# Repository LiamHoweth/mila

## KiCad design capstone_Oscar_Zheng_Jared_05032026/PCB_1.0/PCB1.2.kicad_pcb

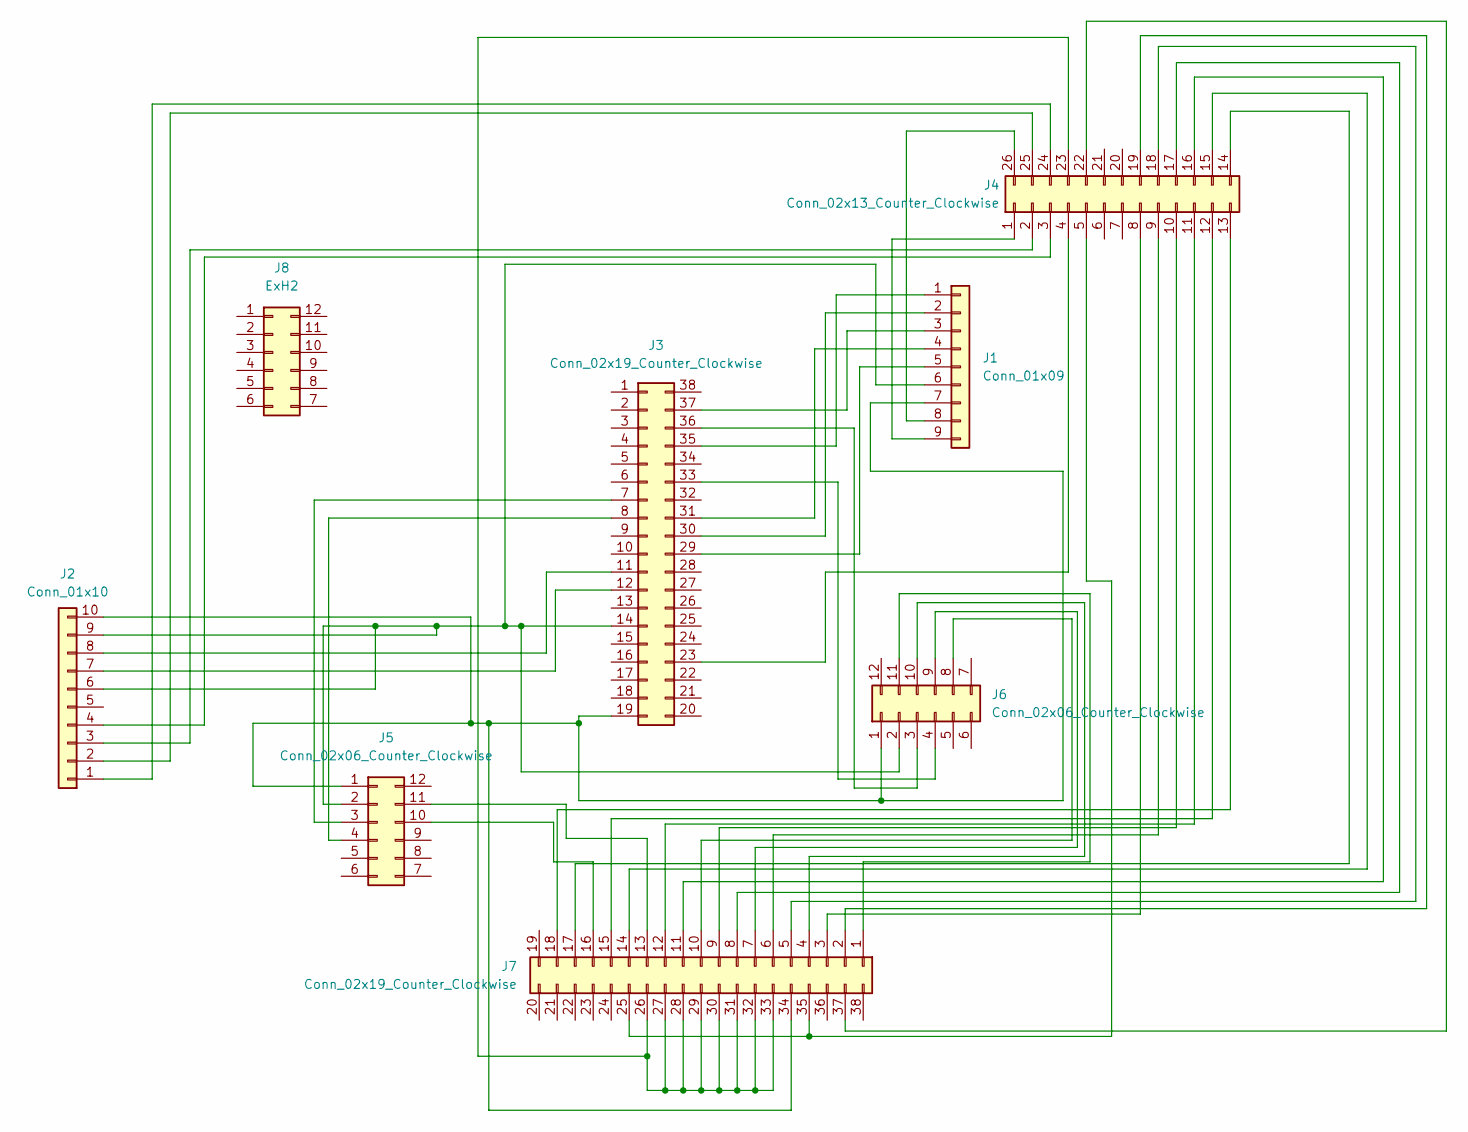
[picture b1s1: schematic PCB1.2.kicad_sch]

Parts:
J1: Conn_01x09; MCP2515
J2: Conn_01x10; ADS1115
J3: Conn_02x19_Counter_Clockwise; ESP-32
J4: Conn_02x13_Counter_Clockwise; MX23A26NF1
J5, J6: Conn_02x06_Counter_Clockwise; MCP4728
J7: Conn_02x19_Counter_Clockwise; 8-Relay Module
J8: ExH2; ExH12

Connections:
unnamed: J1.1, J3.35
unnamed: J1.2, J3.30
unnamed: J1.3, J3.37
unnamed: J1.4, J3.31
unnamed: J1.5, J3.29
unnamed: J1.6, J2.6, J2.9, J3.14, J5.2, J6.2
unnamed: J1.7, J2.10, J3.19, J5.1, J6.1, J7.34
unnamed: J1.8, J4.26
unnamed: J1.9, J4.1
unnamed: J2.1, J4.24
unnamed: J2.2, J4.25
unnamed: J2.3, J4.2
unnamed: J2.4, J4.3
unnamed: J2.7, J3.12
unnamed: J2.8, J3.11
unnamed: J3.7, J5.3
unnamed: J3.8, J5.4
unnamed: J3.23, J4.4
unnamed: J3.33, J6.4
unnamed: J3.36, J6.3
unnamed: J4.5, J7.25, J7.35
unnamed: J4.8, J7.3
unnamed: J4.9, J7.6
unnamed: J4.10, J7.9
unnamed: J4.11, J7.12
unnamed: J4.12, J7.15
unnamed: J4.13, J7.18
unnamed: J4.14, J7.17
unnamed: J4.15, J7.14
unnamed: J4.16, J7.11
unnamed: J4.17, J7.8
unnamed: J4.18, J7.5
unnamed: J4.19, J7.2
unnamed: J4.22, J7.37
unnamed: J4.23, J7.26, J7.27, J7.28, J7.29, J7.30, J7.31, J7.32, J7.33
unnamed: J5.10, J7.16
unnamed: J5.11, J7.13
unnamed: J6.8, J7.10
unnamed: J6.9, J7.7
unnamed: J6.10, J7.4
unnamed: J6.11, J7.1

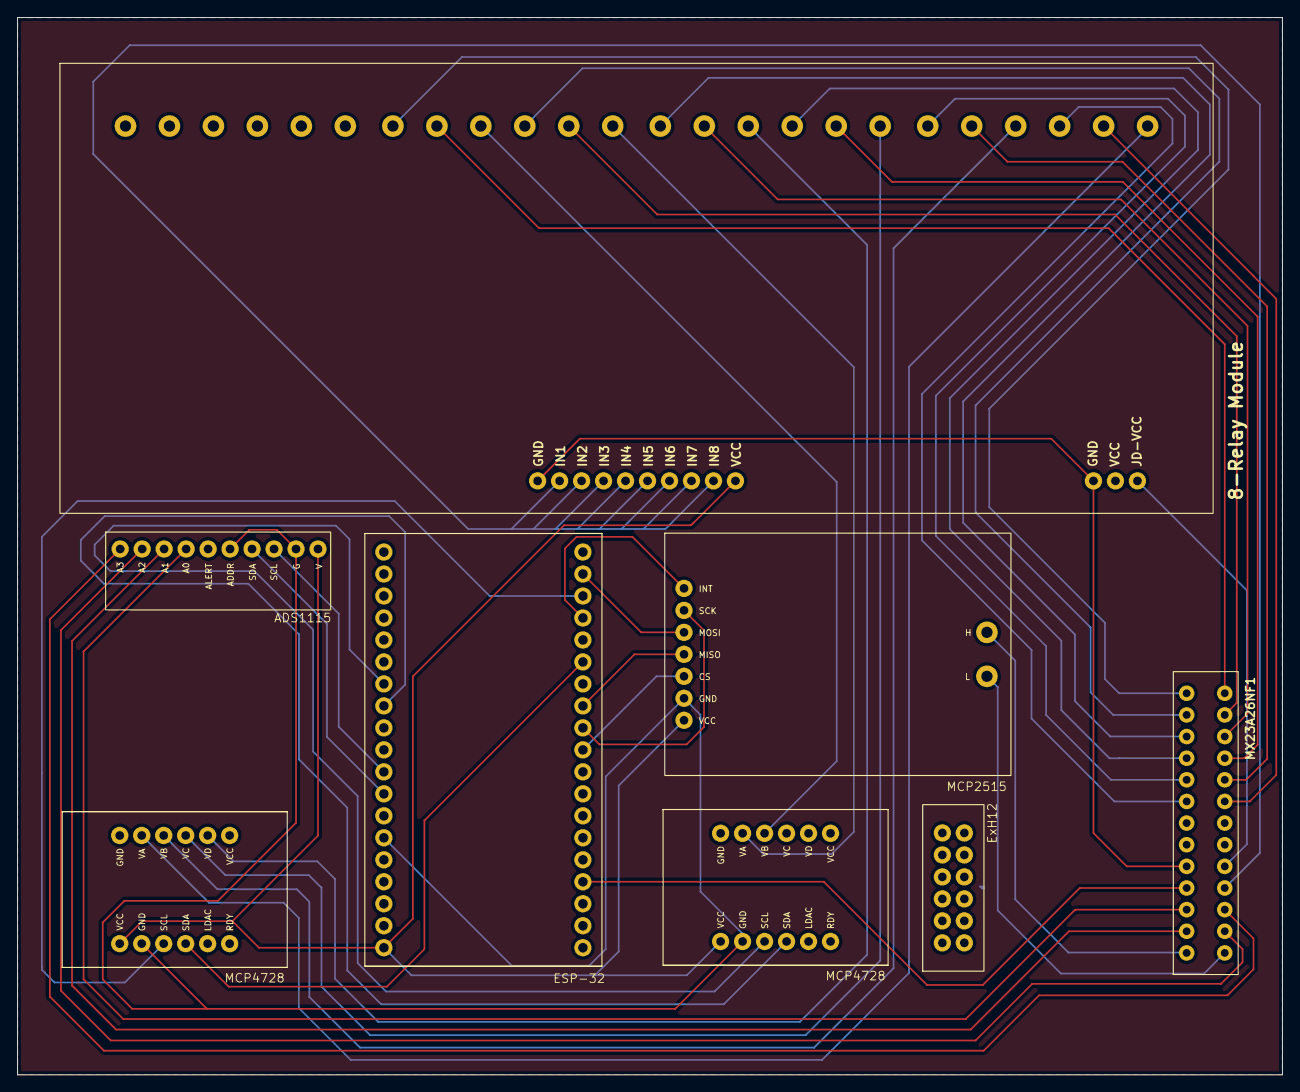
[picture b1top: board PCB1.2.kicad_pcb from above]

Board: 2 copper layers, 146.2 x 122.2 mm, 8 parts (0 on the bottom side), 41 nets.

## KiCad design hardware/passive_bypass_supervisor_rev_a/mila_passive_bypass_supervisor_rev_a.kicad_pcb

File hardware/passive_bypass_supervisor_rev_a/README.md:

# MiLa external relay supervisor — bench Rev A

This auxiliary circuit inhibits relay-coil power until rail health, a windowed firmware heartbeat, READY, held physical enable, and a fresh physical ARM press are present. It clears permission on a recognized fault and requires another ARM press after recovery. It is an isolated, room-temperature simulator prototype. Neither this circuit nor a passing CAD check establishes vehicle safety, uninterrupted signals, contact position, or independent command plausibility.

The schematic contains complete manufacturer-numbered pin connections and passive values. Custom pin-block symbols preserve real pin electrical types; identical named nets are connected. `pin_net.csv` and `netlist.xml` expose the actual circuit for audit. The carrier contains the coil drivers and four nonlatching DPDT relays. This supervisor has no signal contacts or ESP socket. The routed 80 × 60 mm, two-layer PCB has 64 circuit parts plus four mounting holes. Native ERC, DRC, unconnected-item and schematic-parity checks are all zero. Physical assembly and validation remain pending.

## Files and reproduction

- `mila_passive_bypass_supervisor_rev_a.kicad_sch`: editable complete circuit.
- `schematic.pdf` and `svg/`: exported schematic.
- `MiLaBench.kicad_sym`, `sym-lib-table`, `.kicad_pro`: local symbol library/project.
- `bom.csv`, `pin_net.csv`, `circuit.json`: parts, pin connections and board-generator input.
- `netlist.xml`: KiCad-exported connectivity, rather than a copy of the generator manifest.
- `erc.rpt`: KiCad electrical-rules report. No ERC exclusions are used.
- `bench_expectations.csv`: 33 physical probes, all PENDING.
- `.kicad_pcb`, project-local `.pretty` libraries and `fp-lib-table`: editable routed layout and local footprint copies.
- `pcb_validation/`: native checks, recorded export commands, final routing metrics and top/bottom/assembly previews.
- `manufacture/`: Gerbers, separate plated/unplated drill files, drill maps/report and positions CSV.

From the canonical MiLa directory:

```sh
python3 tools/build_passive_bypass_supervisor.py
/Applications/KiCad/KiCad.app/Contents/MacOS/kicad-cli sch erc --severity-all --exit-code-violations --output hardware/passive_bypass_supervisor_rev_a/erc.rpt hardware/passive_bypass_supervisor_rev_a/mila_passive_bypass_supervisor_rev_a.kicad_sch
/Applications/KiCad/KiCad.app/Contents/MacOS/kicad-cli sch export netlist --format kicadxml --output hardware/passive_bypass_supervisor_rev_a/netlist.xml hardware/passive_bypass_supervisor_rev_a/mila_passive_bypass_supervisor_rev_a.kicad_sch
python3 tools/build_passive_bypass_supervisor.py --verify-netlist hardware/passive_bypass_supervisor_rev_a/netlist.xml
```

The final schematic checkpoint has zero ERC violations. The explicit verifier checks 207 connected component pins and nine intentionally unconnected pins against KiCad's export. Supply flags describe externally or passively driven rails; they do not represent extra physical devices. CAD checks do not test timing, startup glitches, relay transfer, current ratings or analog outputs.

Rebuild the accepted supervisor PCB with KiCad's bundled Python:

```sh
/Applications/KiCad/KiCad.app/Contents/Frameworks/Python.framework/Versions/3.9/bin/python3.9 tools/build_passive_bypass_supervisor_board.py
```

The default rebuild uses `pcb_validation/accepted_layout.json`, containing the
accepted trace/via geometry and circuit/footprint hashes. A reconstruction from
a fresh board object passed native checks and exports. The hash guard rejects
changed circuit or footprint inputs: preserve the frozen source/export files
when reproducing this revision. A new schematic/netlist export may change
metadata hashes even when its electrical connections are equivalent; inspect
and validate a revised layout rather than bypassing that guard.

Use `--validate-existing` to check/export the saved PCB. `--reroute` invokes
exploratory routing and can require local repair; it is not the accepted build
path. The final board uses 0.25 mm tracks, 0.20 mm clearance, 0.70/0.30 mm vias
and four 3.2 mm unplated mounting holes. Actual power-pin decouplers are
approximately 1.89–2.51 mm away. The heartbeat clock uses a shared trunk with
7.3625/7.9375 mm branches; measured geometry skew is 0.575 mm. Geometry alone
does not establish propagation, setup/hold or asynchronous-edge acceptance.

## Supply and connector contract

Use a protected, current-limited 5.0 V bench supply, with 4.95–5.25 V available for guaranteed monitor recovery margin, and a shared ESP 3.3 V rail. Nominal room-temperature assembly testing uses 5.0 V and 3.3 V at 20–30°C. The monitor can inhibit arming at 4.75 V even if that voltage is allowed at the carrier. Maintain a common ground. Do not apply raw vehicle power. The upstream 5 V rail supplies the DAC system and one input of the U3 supply OR; it is separate from the switched coil feed. U13 is powered from 3.3 V.

| Connector | Pin sequence | Meaning |
|---|---|---|
| J1, 1×8 | 1 GND; 2 V3V3; 3 ESP_RESET_HEADER; 4 WDI_HEADER; 5 READY_HEADER; 6 REQ_L; 7 REQ_7; 8 REQ_8 | Controller interface. Explicit GPIO mapping belongs to the controller wiring manifest. |
| J2, 1×2 | 1 V5_SUP; 2 GND | Upstream protected regulated 5 V. |
| J3, 1×4 | 1 V5_SUP; 2 V5_COIL_SWITCHED; 3 V3V3; 4 DEADMAN_HEADER | External held two-pole normally-open enable: coil pole connects 1–2, auxiliary pole connects 3–4 only while held. |
| J4, 1×2 | 1 ARM_SW; 2 GND | Separate physical normally-open ARM button. |
| J5, 1×7 | 1 GND; 2 V5_COIL_SWITCHED; 3 COIL_PERMIT; 4 REQ_L; 5 REQ_7; 6 REQ_8; 7 CARRIER_5V_FEEDBACK | Carrier interface, including returned post-enable coil input. Match functions, not arbitrary connector pin numbers. |
| J6, 1×6 | 1 GND; 2 HEALTH_OK; 3 QUALIFIED; 4 HB_GOOD; 5 ARMED; 6 ZERO_REQ | 3.3 V status/test points. |

The generic 2.54 mm headers are bench connectors. Give the physical harness keyed connectors, strain relief and clear pin labels before any later integration. For J3 select **C&K 8221SHZGE**, a held DPDT momentary pushbutton using its two normally-open contacts only. Its gold-over-silver contacts support both 1 A at 28 V DC power switching and low-level/dry-circuit use; the auxiliary contact switches about 0.33 mA at 3.3 V. The manufacturer warns that the two poles need not make/break simultaneously. Connect J3-1 to switch COM1, J3-2 to NO2, J3-3 to COM4, and J3-4 to NO5. Insulate unused NC3 and NC6. Verify purchased terminal identity by continuity: released 1–3/4–6, pressed 1–2/4–5. A stable toggle or a firmware switch does not implement this held-enable requirement.

For J4 select **C&K 8125SHZBE**, a gold-contact SPDT momentary pushbutton: J4-1 to COM1, J4-2 to NO2, with NC3 insulated. Its 0.4 VA/20 V maximum dry-circuit rating covers the approximately 3.3 mA initial ARM-capacitor discharge and about 33 µA held current. Use insulated short 22 AWG leads, panel mounting and strain relief; label the independent buttons ENABLE and ARM. `external_bom.csv` records these off-board parts. Do not jumper J3 for acceptance testing that claims a physical power cut.

J5 must be wired by function to the carrier `GND`, `5V_RAW`, `COIL_PERMIT`, `REQ_GROUP`, `REQ_K7`, `REQ_K8`, and returned `5V_RAW` inputs respectively. `V5_COIL_SWITCHED` is the carrier's `5V_RAW`; it must not also be tied to upstream V5_SUP. J5-7 is returned through the carrier control connector JCTRL1-6 and tied directly to the carrier's post-physical-enable, pre-Q5 `5V_RAW`. Do not loop J5-7 to J5-2 locally: that would defeat control-connector continuity detection. This is a 5 V sense conductor to R22, never an ESP signal. Connect no downstream bulk storage capacitor to the coil feed. No USB, ESP 5 V pin, DAC rail or other source may backfeed it.

READY/WDI/request inputs are nominal 3.3 V and use short local wires. The assembled supervisor adds a 10 kΩ ground load to each request; the carrier adds further loads, particularly two driver loads to REQ_GROUP. Verify controller HIGH ≥2.60 V and carrier MOSFET gate ≥2.50 V under the complete loading. Contact-board input tolerance of 5.25 V does not permit applying 5 V to a connected ESP GPIO.

COIL_PERMIT is a supervisor-generated nominal 3.3 V signal intended solely for the carrier's AO3400A permission gate. Keep it separate from ESP GPIOs and status points. CARRIER_5V_FEEDBACK is a distinct 5 V wire that must never connect to the ESP.

## Exact supervision and state behavior

U1, TPS3430WQDRCRQ1, is the external window watchdog. Both VDD pins and its exposed pad are connected. R1 = 10 kΩ pulls CWD high; SET0 and SET1 are hard-wired low; R2 = 10 kΩ pulls CRST high. No GPIO can disable the watchdog. The falling-edge interval's lower bound is 7.65–10.35 ms and upper bound is 92.7–125.4 ms. Use 30 ms between falling edges, with a 1 ms HIGH pulse, after successful completion of three 10 ms application iterations. WDO remains low for 8.5–11.5 ms after a watchdog fault. It automatically attempts recovery, but the ARM latch does not automatically recover.

The watchdog startup has special timing: WDO is held low during startup/reset; the first subsequent falling WDI edge starts a window whose lower-bound check is suppressed. The separate heartbeat qualification is therefore necessary. A static HIGH/LOW cannot establish ongoing health. Do not generate WDI using a free-running timer, PWM, DMA or an interrupt that can continue after the actual test-control loop hangs.

U2, TPS3808G33QDBVRQ1, monitors the shared 3.3 V rail and the ESP hardware reset/enable line through its MR pin. Its nominal rail trip is 3.07 V; threshold tolerance and hysteresis apply. R3 = 100 kΩ to V3V3 selects nominal 300 ms release delay (180–420 ms specified). Connecting to an actual shared ESP rail is essential; a separate always-on supervisor rail would not detect loss of the controller's own 3.3 V.

U3, TPS3808G01QDBVRQ1, monitors **CARRIER_5V_FEEDBACK** through R22 = 100 kΩ 0.1% and R23 = 9.53 kΩ 0.1%. This observes actual coil input downstream of the physical switch and both complete carrier connectors. Sustained loss of either complete power/control connector causes this divider to fall; after the monitor recognizes the loss and clears the latch, reconnection cannot resume the previous armed state. Contact chatter shorter than the SENSE filter and supervisor recognition time need not latch a fault. C17 = 1 nF filters SENSE with about 8.7 µs nominal RC. Falling trip is nominal 4.655 V. IC accuracy and divider tolerances permit roughly 4.55–4.76 V trip; maximum hysteresis can make recovery require approximately 4.90 V. Use at least 4.95 V for arming, rather than treating 4.75 V as guaranteed recovery.

D1, BAS70-05-7-F, supplies U3 from an isolated OR of both rails: pin 1 anode V3V3, pin 2 anode V5_SUP, pin 3 common cathode V_PG5_SUP. U3's VDD, MR pull-high, CT/R4 and C3 use V_PG5_SUP. This keeps U3 powered when 5 V vanishes but USB keeps 3.3 V alive, and also keeps its SENSE below its supply when 5 V is present while 3.3 V is absent. A fixed G50 powered only from 5 V loses a defined output when its own supply collapses; powering it from 3.3 V while sensing 5 V would exceed recommended SENSE≤VDD. The divider plus diode OR removes those live-rail conflicts. Measure V_PG5_SUP and backfeed in every power sequence; do not infer behavior in the unspecified near-zero-supply region from absolute maximum ratings.

U1 WDO, U2 RESET and U3 RESET are open-drain and share HEALTH_N, pulled to V3V3 by R5 = 10 kΩ. No push-pull output is tied to that node. U4 is a Schmitt buffer for the open-drain edge; U5 buffers the physical-enable sense. U8/U9 form:

```text
QUALIFIED = HEALTH_OK AND READY AND DEADMAN_OK
ZERO_REQ  = NOT(REQ_L OR REQ_7 OR REQ_8)
```

QUALIFIED drives the asynchronous active-low clear pins on both U10 heartbeat stages and the U11 ARM latch. Recognized rail/reset/watchdog/READY/enable loss therefore clears both heartbeat qualification and ARM.

U6 inverts WDI so its falling edge clocks both U10 stages. The first accepted edge after qualification sets HB_ONE. R24 = 1 kΩ, C18 = 100 pF C0G 5%, and U14 SN74LVC1G17QDCKRQ1 delay and buffer HB_ONE into HB_ONE_SAFE before the second D input. A later accepted falling edge sets HB_GOOD. This observations chain requires a full inter-edge interval after READY and held enable; it does not independently prove the semantic validity of a firmware iteration.

R24/C18 provide approximately 100 ns nominal RC plus buffer delay, preserving positive same-clock hold margin. At the datasheet's 3 V threshold test point, U14 VT+ = 1.36–2.04 V, VT− = 0.77–1.35 V; U14 propagation is 1.5–8 ns at 3.3 V ±0.3 V. Use the actual threshold, R/C tolerance, source levels, loading and routing skew to verify:

```text
tCQ(min) + tRC-rise(min) + tU14(min) > tD-hold + positive clock skew
tCQ(max) + tRC-rise(max) + tU14(max) + tD-setup < next heartbeat interval
tRC-fall(max) + tU14(max) < minimum qualified-low time before a new heartbeat
```

The LVC74A requires data setup ≥3 ns, hold ≥1 ns, clear-inactive setup ≥2 ns and clear/clock pulse duration ≥3.3 ns at 3.3 V ±0.3 V. Its clock-to-Q is 1–5.2 ns. The exact 3.3 V Schmitt threshold and slow-edge delay are not separately bounded by the table's 3 V threshold row; measure the actual stage rather than asserting an interpolated certified limit. For the bench protocol, require QUALIFIED LOW ≥10 µs, hold request/READY states stable ≥1 ms before ARM, and start post-recovery heartbeat edges ≥1 ms after qualification. Hardware rail/watchdog release delays greatly exceed RC flush time. Test coincident asynchronous edges separately.

U12 sets ARM_D = HB_GOOD AND ZERO_REQ. U11 captures this only on a physical ARM rising edge. R6 = 100 kΩ, R7 = 1 kΩ and C14 = 1 µF form the ARM network; U6's Schmitt inverter makes pressing the normally-open button produce that edge. Press discharge is about 1 ms and release is about 100 ms nominal, subject to thresholds and capacitance. Verify actual contact bounce. A button held through a fault remains a constant clock level: restoring QUALIFIED does not create a fresh ARM clock edge. Release the button long enough for ARM_CLK to return LOW, then press it again. Requests must be LOW at this new edge.

U13 **SN74LVC1G08QDCKRQ1**, powered from V3V3, produces COIL_PERMIT only when ARMED AND QUALIFIED are high. R18 = 1 kΩ limits initial gate current; R19 = 82 kΩ and the carrier's RPD6 = 82 kΩ pull permission LOW while keeping static loading light. The carrier RG6 remains 330 Ω; R20/R21 remain 10 kΩ input pulldowns; C13 bypasses V3V3. This avoids relying on a 5 V AHCT driver's undefined behavior below its 4.5 V operating range during 5 V collapse.

TI's current LVC1G08-Q1 Rev H specifies recommended-temperature VOH ≥VCC−0.15 V at 100 µA, and Ioff ≤10 µA magnitude at VCC=0. With both 82 kΩ pulldowns, the complete static load is at most approximately **86.51 µA** at VCC=3.6 V, including 1% resistor corners and 100 nA MOSFET gate leakage. At VCC=3.0 V, VOH≥2.85 V produces calculated header ≥**2.78085 V** and Q6 gate ≥**2.76944 V**. Add no output indicator or other DC load that invalidates the 100 µA limit.

At VCC=0, a 10 µA source-like Ioff and 100 nA gate leakage give calculated Q6 gate ≤**0.41743 V** with intact pulldowns. This is a **leakage-voltage screening calculation, not a drain-current OFF guarantee**: the MOSFET threshold is measured at a specified drain current and does not bound drain current at this gate voltage. Opening either pulldown also reduces the margin. Measure Q6/Q5 gate voltage, drain behavior and coil current with V3V3=0/V5 present and through every partial 3.3 V ramp. Typical MOSFET capacitance can suggest approximately 26 µs discharge settling, but does not establish a bounded cutoff time. All these values are calculations awaiting physical validation.

## Firmware and physical boundaries

Boot/reset must keep READY and all relay requests LOW. Raise READY only after successful DAC initialization, acknowledgment of every required write, fresh command and communication checks, and measured simulator output acceptance. Stop WDI when the guarded control iteration fails. The existing autonomous AutoSweep source does not implement this contract and must not directly drive the new interface. READY LOW inhibits DAC absence only if firmware detects it and lowers READY. An ESP that keeps READY HIGH and valid WDI pulses while writing an incorrect DAC value remains outside this supervisor's detection capability.

Physical deadman release disconnects coil power even if the ARM latch or permission electronics fail high. The auxiliary contact also clears the latch. The returned carrier supply detects whole-connector loss but cannot detect an individual broken request/permission conductor while the feedback conductor stays connected. Such a conductor can resume its previously asserted state on reconnection; shorted feedback can conceal connector loss. Pole timing mismatch, welded enable contacts, stored energy, wiring shorts and backfeed remain physical test/fault-analysis matters. Releasing a nonlatching relay eventually restores its NC connection only with healthy contacts; the delay and bounce are finite. K7/K8 NC states are default connectivity, not a verified motor-off or stock-safe behavior.

The settled Boolean state model assumes valid voltages, valid minimum pulse widths, setup/hold/recovery timing and settled inputs. It cannot prove absence of metastability, narrow output pulses during arbitrary power ramps, asynchronous coincidences or stuck component faults. Bench acceptance must scope the real COIL_PERMIT, gate, coil current and every COM signal through those cases. The current design has one watchdog, one fault node and a single permission chain; it is not redundant or single-fault tolerant.

## Primary sources

- [TI TPS3430-Q1 watchdog, pins, startup and timing](https://www.ti.com/lit/ds/symlink/tps3430-q1.pdf)
- [TI TPS3808-Q1 supervisors, G01 divider, timing and supply limits](https://www.ti.com/lit/ds/symlink/tps3808-q1.pdf)
- [TI SN74LVC74A-Q1 flip-flops and timing](https://www.ti.com/lit/ds/symlink/sn74lvc74a-q1.pdf)
- [TI SN74LVC1G17-Q1 Schmitt buffers](https://www.ti.com/lit/ds/symlink/sn74lvc1g17-q1.pdf)
- [TI SN74LVC2G14-Q1 Schmitt inverters](https://www.ti.com/lit/ds/symlink/sn74lvc2g14-q1.pdf)
- [TI SN74LVC1G08-Q1 AND gates](https://www.ti.com/lit/ds/symlink/sn74lvc1g08-q1.pdf)
- [TI SN74LVC1G27 NOR gate](https://www.ti.com/lit/ds/symlink/sn74lvc1g27.pdf)
- [Diodes Incorporated BAS70-05 common-cathode array](https://www.diodes.com/datasheet/download/BAS70.pdf)
- [C&K 8020 momentary pushbuttons, pin numbers and contact ratings](https://www.ckswitches.com/media/1397/8020.pdf)
- [C&K exact 8221SHZGE and 8125SHZBE selection guide](https://www.ckswitches.com/media/2222/ck_short-form-catalogue.pdf)

U7 and D1 use catalog order codes; selecting several Q1 logic devices does not make the whole board automotive-qualified. Verify purchase availability, exact markings, all footprints and manufacturer revisions before assembly.

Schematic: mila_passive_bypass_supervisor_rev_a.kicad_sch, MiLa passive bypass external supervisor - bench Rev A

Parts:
C1, C2, C3, C4, C5, C6, C7, C8, C9, C10, C11, C12, C13, C19: 100nF X7R 10V; C_0603_1608Metric
C14, C15, C16: 1uF X7R 10V; C_0603_1608Metric
C17: 1nF C0G 10V; C_0603_1608Metric
C18: 100pF C0G 5% 10V; C_0603_1608Metric
D1: BAS70-05-7-F; SOT-23
J1: BENCH_1x08; PinHeader_1x08_P2.54mm_Vertical
J2, J4: BENCH_1x02; PinHeader_1x02_P2.54mm_Vertical
J3: BENCH_1x04; PinHeader_1x04_P2.54mm_Vertical
J5: BENCH_1x07; PinHeader_1x07_P2.54mm_Vertical
J6: BENCH_1x06; PinHeader_1x06_P2.54mm_Vertical
R1, R2, R5, R8, R9, R10, R11, R12, R13, R20, R21: 10k 1%; R_0603_1608Metric
R3, R4, R6: 100k 1%; R_0603_1608Metric
R7, R16, R18, R24: 1k 1%; R_0603_1608Metric
R14, R15, R17: 100 1%; R_0603_1608Metric
R19: 82k 1%; R_0603_1608Metric
R22: 100k 0.1%; R_0603_1608Metric
R23: 9.53k 0.1%; R_0603_1608Metric
U1: TPS3430WQDRCRQ1; VSON-10-1EP_3x3mm_P0.5mm_EP1.65x2.4mm
U2: TPS3808G33QDBVRQ1; SOT-23-6
U3: TPS3808G01QDBVRQ1; SOT-23-6
U4, U5, U14: SN74LVC1G17QDCKRQ1; SOT-353_SC-70-5
U6: SN74LVC2G14IDCKRQ1; SOT-363_SC-70-6
U7: SN74LVC1G27DCKR; SOT-363_SC-70-6
U8, U9, U12, U13: SN74LVC1G08QDCKRQ1; SOT-353_SC-70-5
U10, U11: SN74LVC74AQPWRG4Q1; TSSOP-14_4.4x5mm_P0.65mm

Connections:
/ARMED: J6.5 (ARMED), R20.1, U11.5 (1Q), U13.1 (A)
/ARM_CLK: U6.4 (2Y), U11.3 (1CLK)
/ARM_D: U11.2 (1D), U12.4 (Y)
/ARM_RC: C14.1, R6.2, R7.1, U6.3 (2A)
/ARM_SW: J4.1 (ARM_SW), R7.2
/CARRIER_5V_FEEDBACK: J5.7 (CARRIER_5V_FEEDBACK), R22.1
/COIL_PERMIT: J5.3 (COIL_PERMIT), R18.2, R19.1
/DEADMAN_HEADER: J3.4 (DEADMAN_HEADER), R17.1
/DEADMAN_OK: U5.4 (Y), U9.2 (B)
/DEADMAN_RAW: R8.1, R17.2, U5.2 (A)
/ESP_RESET_HEADER: J1.3 (ESP_RESET_HEADER), R16.1
/ESP_RESET_N: R16.2, U2.3 (MR_N)
/HB_CLK: U6.6 (1Y), U10.3 (1CLK), U10.11 (2CLK)
/HB_GOOD: J6.4 (HB_GOOD), U10.9 (2Q), U12.1 (A)
/HB_ONE: R24.1, U10.5 (1Q)
/HB_ONE_SAFE: U10.12 (2D), U14.4 (Y)
/HB_STAGE_RC: C18.1, R24.2, U14.2 (A)
/HEALTH_N: R5.2, U1.8 (WDO_N), U2.1 (RESET_N), U3.1 (RESET_N), U4.2 (A)
/HEALTH_OK: J6.2 (HEALTH_OK), U4.4 (Y), U8.1 (A)
/HEALTH_READY: U8.4 (Y), U9.1 (A)
/PERMIT_DRIVER: R18.1, U13.4 (Y)
/PG5_CT: R4.2, U3.4 (CT)
/PG33_CT: R3.2, U2.4 (CT)
/QUALIFIED: J6.3 (QUALIFIED), R21.1, U9.4 (Y), U10.1 (1CLR_N), U10.13 (2CLR_N), U11.1 (1CLR_N), U13.2 (B)
/READY: R9.1, R15.2, U8.2 (B)
/READY_HEADER: J1.5 (READY_HEADER), R15.1
/REQ_7: J1.7 (REQ_7), J5.5 (REQ_7), R12.1, U7.3 (B)
/REQ_8: J1.8 (REQ_8), J5.6 (REQ_8), R13.1, U7.6 (C)
/REQ_L: J1.6 (REQ_L), J5.4 (REQ_L), R11.1, U7.1 (A)
/V5_COIL_SWITCHED: J3.2 (V5_COIL_SWITCHED), J5.2 (V5_COIL_SWITCHED)
/V5_SENSE: C17.1, R22.2, R23.1, U3.5 (SENSE)
/WDI: R10.1, R14.2, U1.7 (WDI), U6.1 (1A)
/WDI_HEADER: J1.4 (WDI_HEADER), R14.1
/WD_CRST: R2.2, U1.4 (CRST)
/WD_CWD: R1.2, U1.2 (CWD)
/ZERO_REQ: J6.6 (ZERO_REQ), U7.4 (Y), U12.2 (B)

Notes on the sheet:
BENCH ONLY: regulated 5.0 V + shared ESP 3.3 V; keep disconnected from vehicle.
Hardware: window watchdog + both rail supervisors + physical held enable + READY -> asynchronous latch clear.
Two post-READY WDI falling edges -> HB_GOOD; fresh physical ARM rising edge with requests all LOW -> ARMED.
3.3 V COIL_PERMIT is only for relay gate input. External enable pole J3(1-2) physically interrupts coil power.
J5 pin 7 returns carrier post-enable/pre-cutoff 5 V: R22 monitors actual feed; never connect this 5 V wire to ESP.
A. POWER AND WATCHDOG: rail monitors remain independent of the ESP application.
B. QUALIFICATION AND ARM: asynchronous fault clear; two heartbeat stages; fresh physical ARM edge.
J3: external held DPST-NO enable, no jumper in deployed setup. J4: separate normally-open ARM button.
Output is not a semantic command/plausibility monitor. Driver/relay/ECU timing requires measured bench validation.
C. OUTPUT AND INTERFACES: 3.3 V permission is for the carrier MOSFET gate only; carrier feedback is 5 V.
D. PASSIVES: connected by named nets; place each U's 100 nF physically at its supply pins.
E. SUPPLY FLAGS: rails are externally driven or passively fed; flags are not physical components.

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
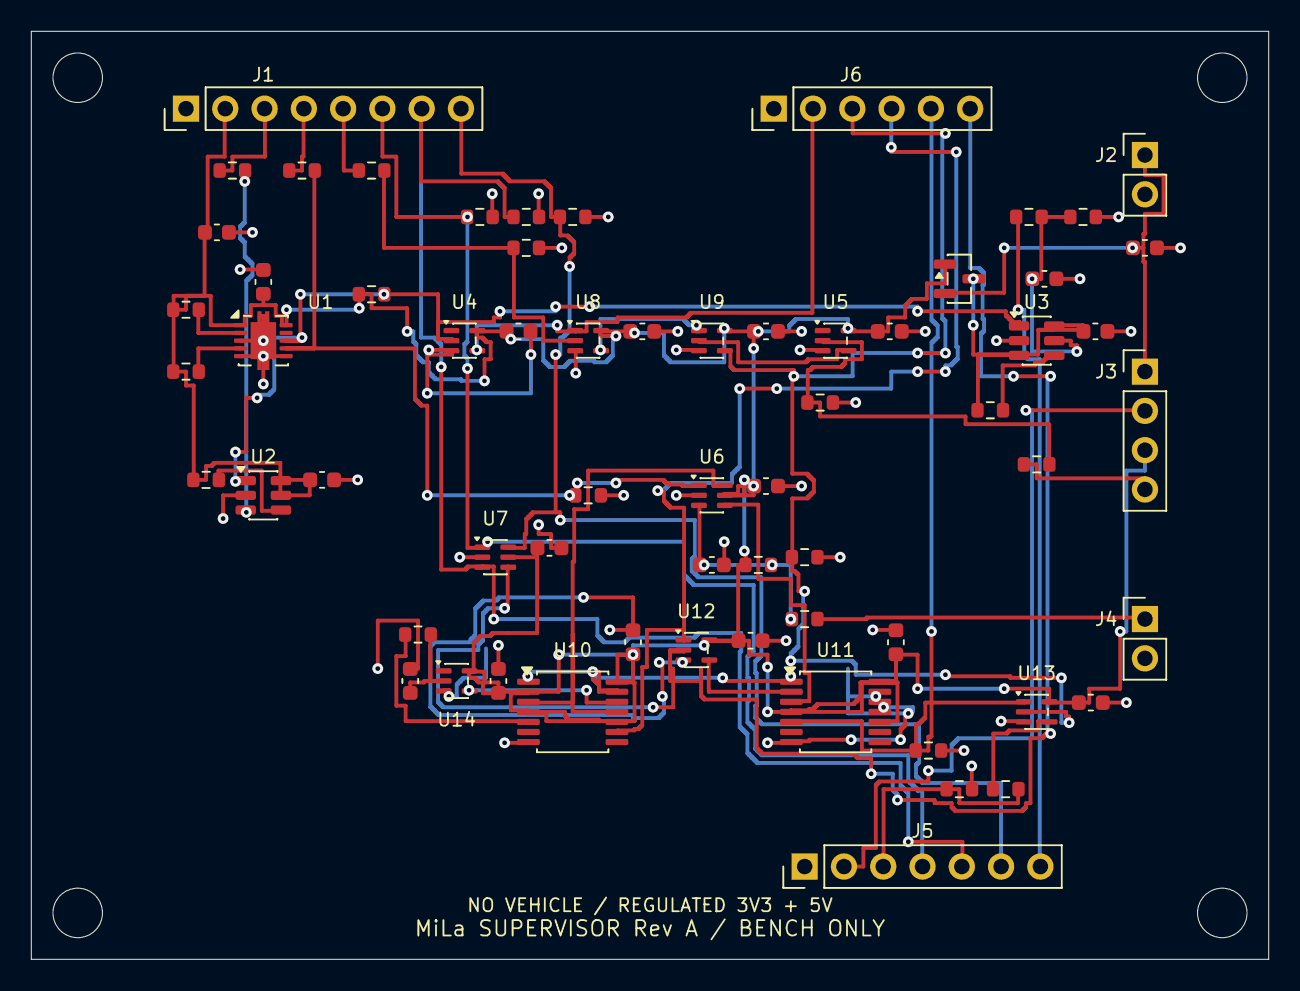
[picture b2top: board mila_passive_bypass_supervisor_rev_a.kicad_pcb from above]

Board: 2 copper layers, 80.0 x 60.0 mm, 68 parts (0 on the bottom side), 40 nets.

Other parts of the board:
H1, H2, H3, H4: MountingHole_3.2mm

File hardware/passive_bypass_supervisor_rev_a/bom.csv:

reference,value,footprint,role,manufacturer_datasheet
U1,TPS3430WQDRCRQ1,Package_SON:VSON-10-1EP_3x3mm_P0.5mm_EP1.65x2.4mm,Independent window watchdog; fixed hardware settings,https://www.ti.com/lit/ds/symlink/tps3430-q1.pdf
U2,TPS3808G33QDBVRQ1,Package_TO_SOT_SMD:SOT-23-6,3.3 V and ESP hardware reset supervisor,https://www.ti.com/lit/ds/symlink/tps3808-q1.pdf
U3,TPS3808G01QDBVRQ1,Package_TO_SOT_SMD:SOT-23-6,5 V adjustable monitor supplied by isolated diode-OR of both rails,https://www.ti.com/lit/ds/symlink/tps3808-q1.pdf
D1,BAS70-05-7-F,Package_TO_SOT_SMD:SOT-23,Low-leakage supply OR keeps 5 V monitor alive when either rail disappears,https://www.diodes.com/datasheet/download/BAS70.pdf
U4,SN74LVC1G17QDCKRQ1,Package_TO_SOT_SMD:SOT-353_SC-70-5,Clean open-drain fault edges before ordinary logic,https://www.ti.com/lit/ds/symlink/sn74lvc1g17-q1.pdf
U5,SN74LVC1G17QDCKRQ1,Package_TO_SOT_SMD:SOT-353_SC-70-5,Clean physical enable auxiliary-contact edges,https://www.ti.com/lit/ds/symlink/sn74lvc1g17-q1.pdf
U6,SN74LVC2G14IDCKRQ1,Package_TO_SOT_SMD:SOT-363_SC-70-6,Invert WDI falling edges and debounce physical ARM,https://www.ti.com/lit/ds/symlink/sn74lvc2g14-q1.pdf
U7,SN74LVC1G27DCKR,Package_TO_SOT_SMD:SOT-363_SC-70-6,All three relay requests must be LOW at ARM edge; catalog bench part,https://www.ti.com/lit/ds/symlink/sn74lvc1g27.pdf
U8,SN74LVC1G08QDCKRQ1,Package_TO_SOT_SMD:SOT-353_SC-70-5,Combine rail/watchdog health and firmware READY,https://www.ti.com/lit/ds/symlink/sn74lvc1g08-q1.pdf
U9,SN74LVC1G08QDCKRQ1,Package_TO_SOT_SMD:SOT-353_SC-70-5,Async clear source includes physical held enable,https://www.ti.com/lit/ds/symlink/sn74lvc1g08-q1.pdf
U10,SN74LVC74AQPWRG4Q1,Package_SO:TSSOP-14_4.4x5mm_P0.65mm,Two WDI falling edges after READY/enable; one full inter-edge cycle,https://www.ti.com/lit/ds/symlink/sn74lvc74a-q1.pdf
U11,SN74LVC74AQPWRG4Q1,Package_SO:TSSOP-14_4.4x5mm_P0.65mm,Manual ARM edge latch; faults clear without automatic restart,https://www.ti.com/lit/ds/symlink/sn74lvc74a-q1.pdf
U12,SN74LVC1G08QDCKRQ1,Package_TO_SOT_SMD:SOT-353_SC-70-5,ARM edge accepted only after heartbeat cycle and zero requests,https://www.ti.com/lit/ds/symlink/sn74lvc1g08-q1.pdf
U13,SN74LVC1G08QDCKRQ1,Package_TO_SOT_SMD:SOT-353_SC-70-5,3.3 V lightly loaded permission driver; output is for carrier gate only,https://www.ti.com/lit/ds/symlink/sn74lvc1g08-q1.pdf
U14,SN74LVC1G17QDCKRQ1,Package_TO_SOT_SMD:SOT-353_SC-70-5,Buffered HB_ONE delay provides positive same-clock DFF hold margin,https://www.ti.com/lit/ds/symlink/sn74lvc1g17-q1.pdf
J1,BENCH_1x08,Connector_PinHeader_2.54mm:PinHeader_1x08_P2.54mm_Vertical,"ESP interface: shared 3.3 V rail, no GPIO mapping assumed",
J2,BENCH_1x02,Connector_PinHeader_2.54mm:PinHeader_1x02_P2.54mm_Vertical,Protected regulated bench 5 V upstream rail,
J3,BENCH_1x04,Connector_PinHeader_2.54mm:PinHeader_1x04_P2.54mm_Vertical,External held enable: pole A 1-2 physically cuts coil feed; pole B 3-4 reports enable,
J4,BENCH_1x02,Connector_PinHeader_2.54mm:PinHeader_1x02_P2.54mm_Vertical,Physical normally-open ARM pushbutton shorts 1-2 only,
J5,BENCH_1x07,Connector_PinHeader_2.54mm:PinHeader_1x07_P2.54mm_Vertical,Relay board interface; physical coil feed and returned carrier 5 V continuity sense,
J6,BENCH_1x06,Connector_PinHeader_2.54mm:PinHeader_1x06_P2.54mm_Vertical,3.3 V test/status points only,
R1,10k 1%,Resistor_SMD:R_0603_1608Metric,Watchdog fixed window setting,
R2,10k 1%,Resistor_SMD:R_0603_1608Metric,Watchdog fixed reset setting,
R3,100k 1%,Resistor_SMD:R_0603_1608Metric,300 ms nominal PG33 reset release,
R4,100k 1%,Resistor_SMD:R_0603_1608Metric,300 ms nominal PG5 reset release,
R5,10k 1%,Resistor_SMD:R_0603_1608Metric,Shared open-drain health pull-up,
R6,100k 1%,Resistor_SMD:R_0603_1608Metric,ARM default released; 100 ms nominal release RC,
R7,1k 1%,Resistor_SMD:R_0603_1608Metric,ARM press current/RC limit,
R8,10k 1%,Resistor_SMD:R_0603_1608Metric,Disconnected enable defaults LOW,
R9,10k 1%,Resistor_SMD:R_0603_1608Metric,READY defaults LOW,
R10,10k 1%,Resistor_SMD:R_0603_1608Metric,WDI defaults LOW,
R11,10k 1%,Resistor_SMD:R_0603_1608Metric,Relay request default LOW,
R12,10k 1%,Resistor_SMD:R_0603_1608Metric,Relay request default LOW,
R13,10k 1%,Resistor_SMD:R_0603_1608Metric,Relay request default LOW,
R14,100 1%,Resistor_SMD:R_0603_1608Metric,Short local WDI wire series damping,
R15,100 1%,Resistor_SMD:R_0603_1608Metric,Short local READY wire series damping,
R16,1k 1%,Resistor_SMD:R_0603_1608Metric,ESP hardware reset input current limit,
R17,100 1%,Resistor_SMD:R_0603_1608Metric,Physical enable sense series damping,
R18,1k 1%,Resistor_SMD:R_0603_1608Metric,Permit initial MOS gate-current limit and series damping,
R19,82k 1%,Resistor_SMD:R_0603_1608Metric,Light permission load; parallel carrier 82k provides passive LOW,
R20,10k 1%,Resistor_SMD:R_0603_1608Metric,Permit-gate ARMED input passive LOW,
R21,10k 1%,Resistor_SMD:R_0603_1608Metric,Permit-gate QUALIFIED input passive LOW,
R22,100k 0.1%,Resistor_SMD:R_0603_1608Metric,Returned carrier 5 V divider upper resistor; ~4.655 V threshold,
R23,9.53k 0.1%,Resistor_SMD:R_0603_1608Metric,5 V monitor divider lower resistor,
R24,1k 1%,Resistor_SMD:R_0603_1608Metric,Heartbeat stage hold-time margin delay,
C1,100nF X7R 10V,Capacitor_SMD:C_0603_1608Metric,Place at U1 supply pin(s),
C2,100nF X7R 10V,Capacitor_SMD:C_0603_1608Metric,Place at U2 supply pin(s),
C3,100nF X7R 10V,Capacitor_SMD:C_0603_1608Metric,Place at U3 supply pin(s),
C4,100nF X7R 10V,Capacitor_SMD:C_0603_1608Metric,Place at U4 supply pin(s),
C5,100nF X7R 10V,Capacitor_SMD:C_0603_1608Metric,Place at U5 supply pin(s),
C6,100nF X7R 10V,Capacitor_SMD:C_0603_1608Metric,Place at U6 supply pin(s),
C7,100nF X7R 10V,Capacitor_SMD:C_0603_1608Metric,Place at U7 supply pin(s),
C8,100nF X7R 10V,Capacitor_SMD:C_0603_1608Metric,Place at U8 supply pin(s),
C9,100nF X7R 10V,Capacitor_SMD:C_0603_1608Metric,Place at U9 supply pin(s),
C10,100nF X7R 10V,Capacitor_SMD:C_0603_1608Metric,Place at U10 supply pin(s),
C11,100nF X7R 10V,Capacitor_SMD:C_0603_1608Metric,Place at U11 supply pin(s),
C12,100nF X7R 10V,Capacitor_SMD:C_0603_1608Metric,Place at U12 supply pin(s),
C13,100nF X7R 10V,Capacitor_SMD:C_0603_1608Metric,Place at U13 supply pin(s),
C14,1uF X7R 10V,Capacitor_SMD:C_0603_1608Metric,ARM debounce capacitor; verify contact bounce on bench,
C15,1uF X7R 10V,Capacitor_SMD:C_0603_1608Metric,Local 3.3 V decoupling; no hold-up promise,
C16,1uF X7R 10V,Capacitor_SMD:C_0603_1608Metric,Upstream 5 V local decoupling; not downstream of enable switch,
C17,1nF C0G 10V,Capacitor_SMD:C_0603_1608Metric,5 V SENSE divider noise filter; ~8.7 us nominal RC,
C18,100pF C0G 5% 10V,Capacitor_SMD:C_0603_1608Metric,Heartbeat stage delay; ~100 ns nominal RC before Schmitt buffer,
C19,100nF X7R 10V,Capacitor_SMD:C_0603_1608Metric,Place at U14 supply pin,
